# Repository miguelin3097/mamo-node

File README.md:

# MAMO NODE — UWB Ranging Node (HW REV A)

Carrier board for a battery-powered **Ultra-Wideband (UWB) ranging node** built around a
**Raspberry Pi Pico 2 W** and a **Qorvo DWM3001CDK**. It turns a hand-wired prototype into a
clean, reproducible PCB designed in **KiCad 10** and assembled by **JLCPCB**.

> Design philosophy: REV A is deliberately the *same circuit as the working wired prototype*,
> moved to a PCB with a minimum of additions. No sophisticated power path, no extra sensors.

---

## Features

- **Plug-in modules:** the Pico 2 W and the DWM3001CDK sit on female headers and can be removed
  without soldering.
- **Single 18650 Li-ion cell** with an off-the-shelf charger + protection + 5 V boost module
  (USB-C charging, can charge and run at the same time).
- **Hardware power-cycle of the DWM3001CDK:** its ground is switched by a low-side N-MOSFET
  driven from a Pico GPIO (full hard reset, not just the RESET pin).
- **Node ID selectable in hardware:** 6-position DIP switch (IDs 1–63), so every node runs the
  same firmware.
- **Battery voltage monitoring** on an ADC pin.
- **Power switch, resettable fuse and power LED.**
- **UWB antenna overhangs the board edge** (no copper underneath), and a copper keep-out under
  the Pico 2 W Wi-Fi/BLE antenna.
- **Test points** for battery, 5 V rail, ground, DWM enable and the switched DWM ground.

## Repository structure

```
.
├── uwb_node_revA/            KiCad 10 project (schematic, PCB, project footprint library)
│   ├── uwb_node_revA.kicad_pro
│   ├── uwb_node_revA.kicad_sch
│   ├── uwb_node_revA.kicad_pcb
│   ├── uwb_node.pretty/      Custom / adapted footprints
│   └── production/           Fabrication outputs (Gerber ZIP, BOM, CPL) for JLCPCB
├── host/                     Python orchestrator (MQTT + Qorvo UCI) that runs on a PC/RPi
├── firmware/                 Pico 2 W firmware notes and interface (see firmware/README.md)
├── docs/
│   ├── hardware.md           Architecture, power, pinout, connectors
│   ├── assembly.md           What JLCPCB mounts and what is assembled by hand
│   ├── ordering-jlcpcb.md    How to regenerate the outputs and order the boards
│   ├── bring-up.md           First power-on and test checklist
│   └── known-issues.md       REV A limitations and ideas for REV B
├── LICENSE
└── README.md
```

## Board at a glance

| Item | Value |
|---|---|
| Size | 100 × 90 mm (+9 mm DWM module overhang on the right edge) |
| Stack-up | 2 layers, 1.6 mm FR-4, lead-free HASL |
| Ground | GND pour on both layers; keep-out under the Pico 2 W antenna |
| Mounting | 3 × M2 holes (H1, H2, H3) + 2 × M2 for the charger module |
| Supply | 1 × 18650 cell → charger/boost module → 5.0 V system rail |
| Main modules | Raspberry Pi Pico 2 W, Qorvo DWM3001CDK |

## Pico 2 W pin assignment

| GPIO | Pico pin | Function |
|---|---|---|
| GP0 | 1 | UART TX → DWM3001CDK J10 pin 8 |
| GP1 | 2 | UART RX ← DWM3001CDK J10 pin 10 |
| GP2 | 4 | DWM power control (HIGH = DWM on) |
| GP10–GP15 | 14–17, 19, 20 | NODE ID bits 0–5 (DIP switch, active-low) |
| GP26 | 31 | Battery voltage sense (÷2 divider) |
| GP4–GP7, GP27, GP28 | 6, 7, 9, 10, 32, 34 | Reserved, routed to J3 (not populated) |
| VSYS | 39 | System supply (from +5V_SYS through a Schottky diode) |
| 3V3 | 36 | Pull-ups for the NODE ID switch, J3 |

Details in [`docs/hardware.md`](docs/hardware.md).

## Opening the design

1. Install **KiCad 10**.
2. Open `uwb_node_revA/uwb_node_revA.kicad_pro`.
3. The project footprint library `uwb_node` is referenced through `${KIPRJMOD}`, so it is found
   automatically.

> Note: a few footprints and 3D models were imported from LCSC/EasyEDA with `easyeda2kicad`
> (see [`docs/known-issues.md`](docs/known-issues.md)). The PCB opens correctly because KiCad
> stores footprints inside the board file, but some 3D models may not render.

## Software

The [`host/`](host/README.md) folder contains the Python orchestrator that coordinates the
ranging sessions over MQTT. Qorvo's SDK files are required but not redistributed (see
`host/README.md`).

## Ordering

The `production/` folder contains the files used for the JLCPCB order (generated with the
**Fabrication Toolkit** plugin). See [`docs/ordering-jlcpcb.md`](docs/ordering-jlcpcb.md).

## Status

- [x] Schematic and PCB (REV A)
- [x] Fabrication files generated and boards ordered (JLCPCB, Standard PCBA)
- [ ] Bring-up and electrical validation
- [ ] Enclosure (3D-printed)
- [x] Host orchestrator published in `host/`
- [ ] Pico 2 W firmware published in `firmware/`

## License

Released under the [MIT License](LICENSE).

## Author

Designed by **Miguel Ángel**.

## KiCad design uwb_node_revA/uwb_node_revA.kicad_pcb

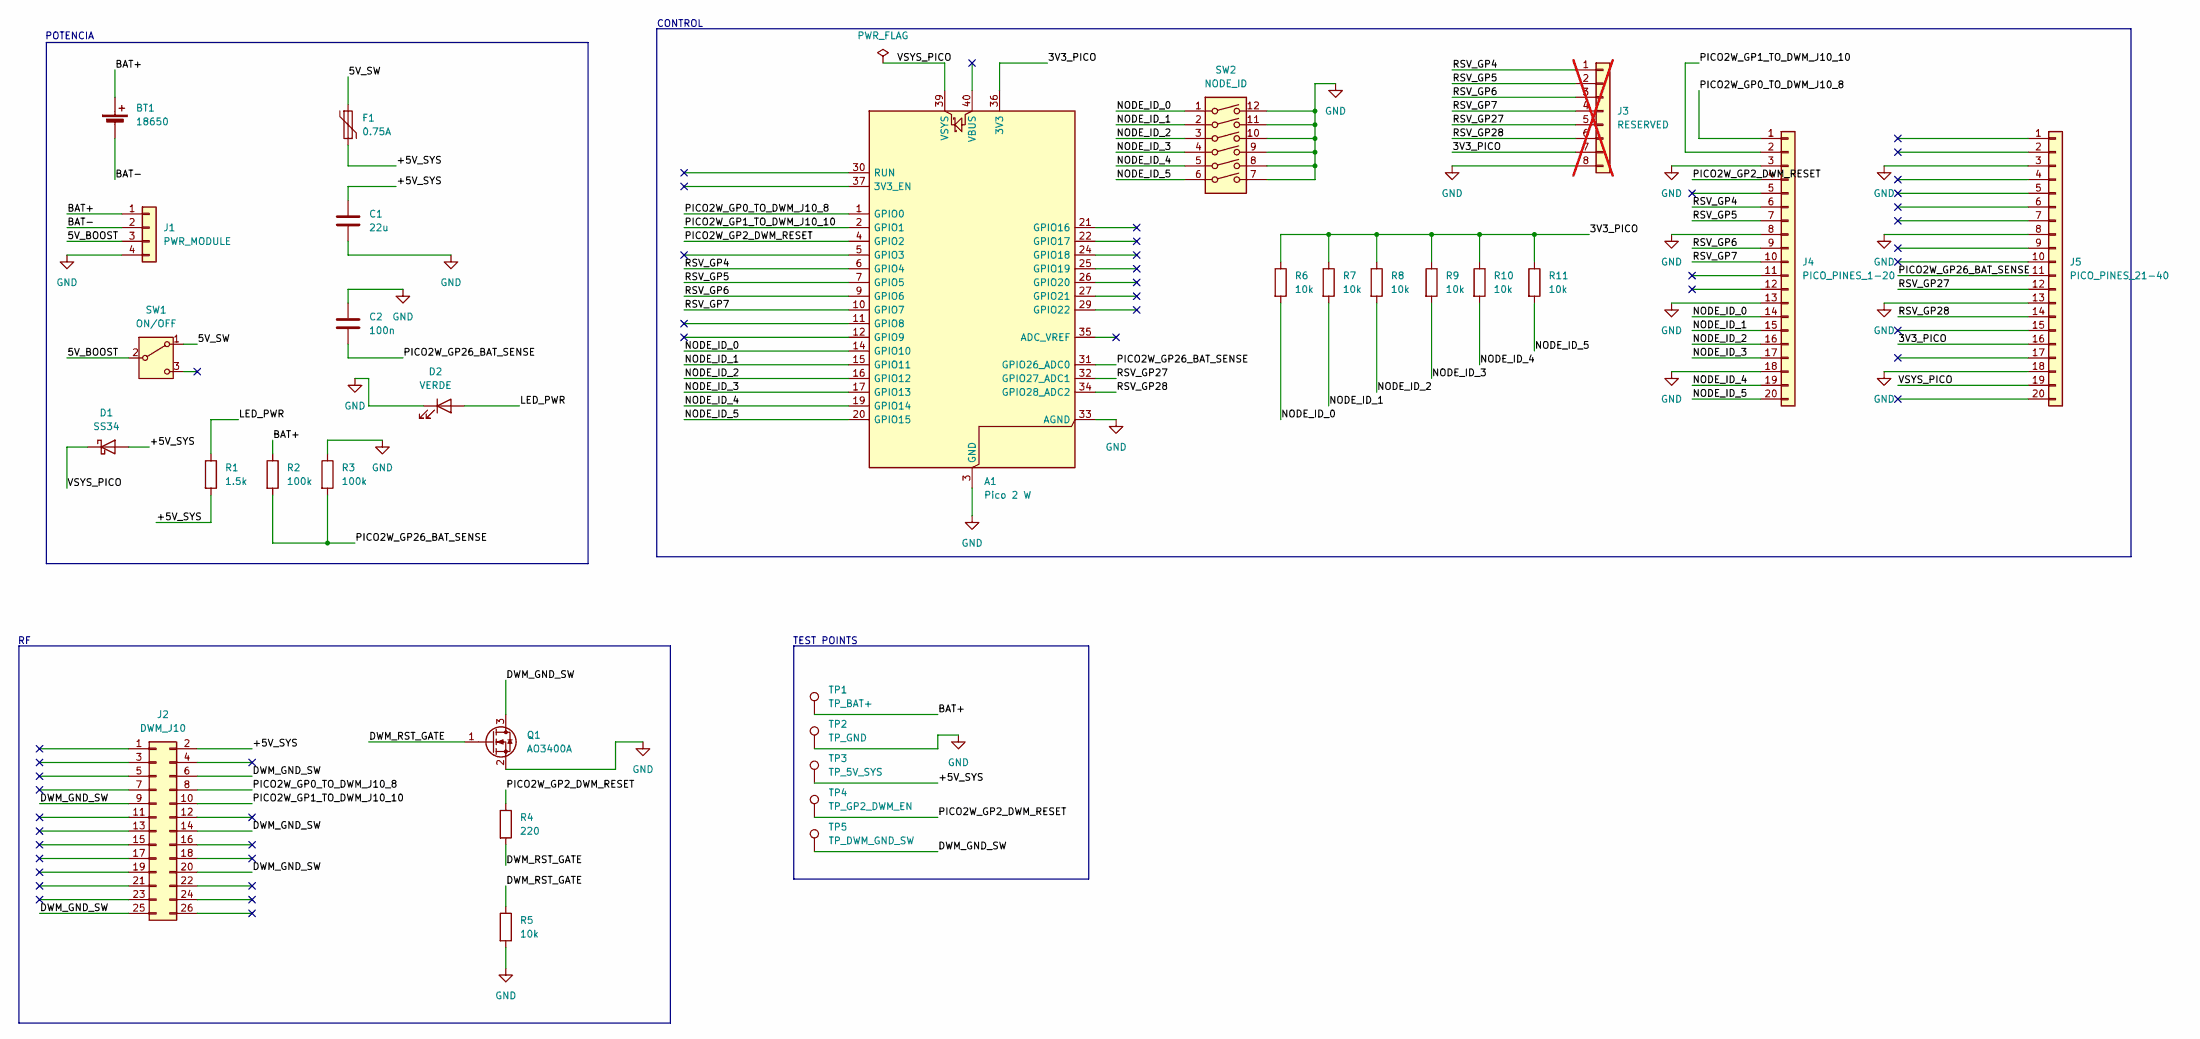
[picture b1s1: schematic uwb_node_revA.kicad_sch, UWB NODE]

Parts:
A1: Pico 2 W; RaspberryPi_Pico_Common_THT
BT1: 18650; BATTERY-SMD_18650-1S-L77.1-W20.7-1; LCSC C2988620
C1: 22u; C_0805_2012Metric; LCSC C45783
C2: 100n; C_0805_2012Metric; LCSC C49678
D1: SS34; D_SMA; LCSC C8678
D2: VERDE; LED_0805_2012Metric; LCSC C2297
F1: 0.75A; Fuse_1206_3216Metric; LCSC C976305
J1: PWR_MODULE; PWR_MODULE_LCBST
J2: DWM_J10; PinHeader_2x13_P2.54mm_Vertical; LCSC C64320
J3: RESERVED; PinHeader_1x08_P2.54mm_Vertical; not fitted
J4: PICO_PINES_1-20; PinSocket_1x20_P2.54mm_Vertical; LCSC C2905423
J5: PICO_PINES_21-40; PinSocket_1x20_P2.54mm_Vertical; LCSC C2905423
Q1: AO3400A; SOT-23; LCSC C20917
R1: 1.5k; R_0805_2012Metric; LCSC C4310
R2, R3: 100k; R_0805_2012Metric; LCSC C149504
R4: 220; R_0805_2012Metric; LCSC C17557
R5, R6, R7, R8, R9, R10, R11: 10k; R_0805_2012Metric; LCSC C17414
SW1: ON/OFF; SW-SMD_MK-12C02-G020; LCSC C963206
SW2: NODE_ID; SW-SMD_12P-L15.2-W6.0-P2.54-LS9.3-BL; LCSC C54952
TP1: TP_BAT+; TestPoint_Pad_D1.5mm
TP2: TP_GND; TestPoint_Pad_D1.5mm
TP3: TP_5V_SYS; TestPoint_Pad_D1.5mm
TP4: TP_GP2_DWM_EN; TestPoint_Pad_D1.5mm
TP5: TP_DWM_GND_SW; TestPoint_Pad_D1.5mm

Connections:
/3V3_PICO: A1.36 (3V3), J3.7, J5.16, R6.1, R7.1, R8.1, R9.1, R10.1, R11.1
/5V_BOOST: J1.3, SW1.2 (B)
/5V_SW: F1.1, SW1.1 (A)
/+5V_SYS: C1.1, D1.2 (A), F1.2, J2.2, R1.2, TP3.1 (1_1)
/BAT+: BT1.1 (+), J1.1, R2.1, TP1.1 (1_1)
/BAT-: BT1.2 (-), J1.2
/DWM_GND_SW: J2.6, J2.9, J2.14, J2.20, J2.25, Q1.3 (D), TP5.1 (1_1)
/DWM_RST_GATE: Q1.1 (G), R4.2, R5.1
/LED_PWR: D2.2 (A), R1.1
/NODE_ID_0: A1.14 (GPIO10), J4.14, R6.2, SW2.1
/NODE_ID_1: A1.15 (GPIO11), J4.15, R7.2, SW2.2
/NODE_ID_2: A1.16 (GPIO12), J4.16, R8.2, SW2.3
/NODE_ID_3: A1.17 (GPIO13), J4.17, R9.2, SW2.4
/NODE_ID_4: A1.19 (GPIO14), J4.19, R10.2, SW2.5
/NODE_ID_5: A1.20 (GPIO15), J4.20, R11.2, SW2.6
/PICO2W_GP0_TO_DWM_J10_8: A1.1 (GPIO0), J2.8, J4.1
/PICO2W_GP1_TO_DWM_J10_10: A1.2 (GPIO1), J2.10, J4.2
/PICO2W_GP2_DWM_RESET: A1.4 (GPIO2), J4.4, R4.1, TP4.1 (1_1)
/PICO2W_GP26_BAT_SENSE: A1.31 (GPIO26_ADC0), C2.2, J5.11, R2.2, R3.2
/RSV_GP4: A1.6 (GPIO4), J3.1, J4.6
/RSV_GP5: A1.7 (GPIO5), J3.2, J4.7
/RSV_GP6: A1.9 (GPIO6), J3.3, J4.9
/RSV_GP7: A1.10 (GPIO7), J3.4, J4.10
/RSV_GP27: A1.32 (GPIO27_ADC1), J3.5, J5.12
/RSV_GP28: A1.34 (GPIO28_ADC2), J3.6, J5.14
/VSYS_PICO: A1.39 (VSYS), D1.1 (K), J5.19
GND: A1.3 (GND), A1.8 (GND), A1.13 (GND), A1.18 (GND), A1.23 (GND), A1.28 (GND), A1.33 (AGND), A1.38 (GND), C1.2, C2.1, D2.1 (K), J1.4, J3.8, J4.3, J4.8, J4.13, J4.18, J5.3, J5.8, J5.13, J5.18, Q1.2 (S), R3.1, R5.2, SW2.7, SW2.8, SW2.9, SW2.10, SW2.11, SW2.12, TP2.1 (1_1)

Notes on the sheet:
CONTROL
TEST POINTS
POTENCIA

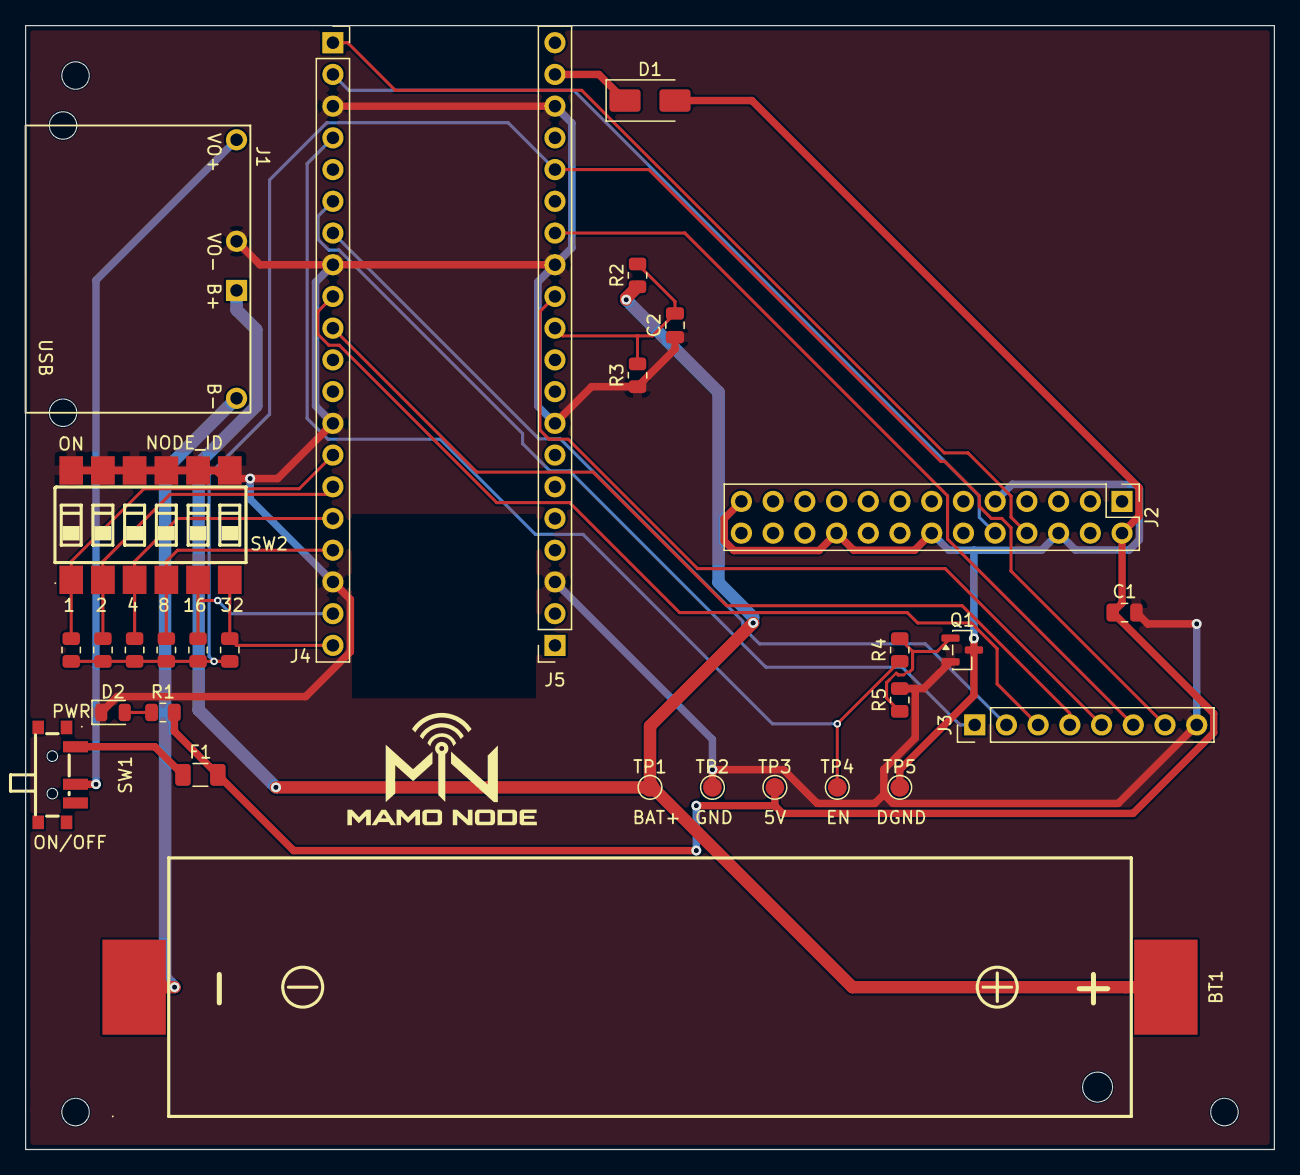
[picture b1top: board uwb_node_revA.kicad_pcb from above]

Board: 2 copper layers, 100.0 x 90.0 mm, 33 parts (0 on the bottom side), 27 nets.

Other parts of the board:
H1, H2, H3: MountingHole_2.2mm_M2
